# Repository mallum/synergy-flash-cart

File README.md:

# Synergy Flash Cart

A 'Flash Cart' for your DK Synergy synth... select & load ROM cartridge .crt files from the root of an SD card.

A single button cycles between .crt files placed on root of a fat formatted sd card. Top backlit character display shows currently active crt file. 

This repository contains the schematics, BOM, source code and 3D print files for a cartridge.

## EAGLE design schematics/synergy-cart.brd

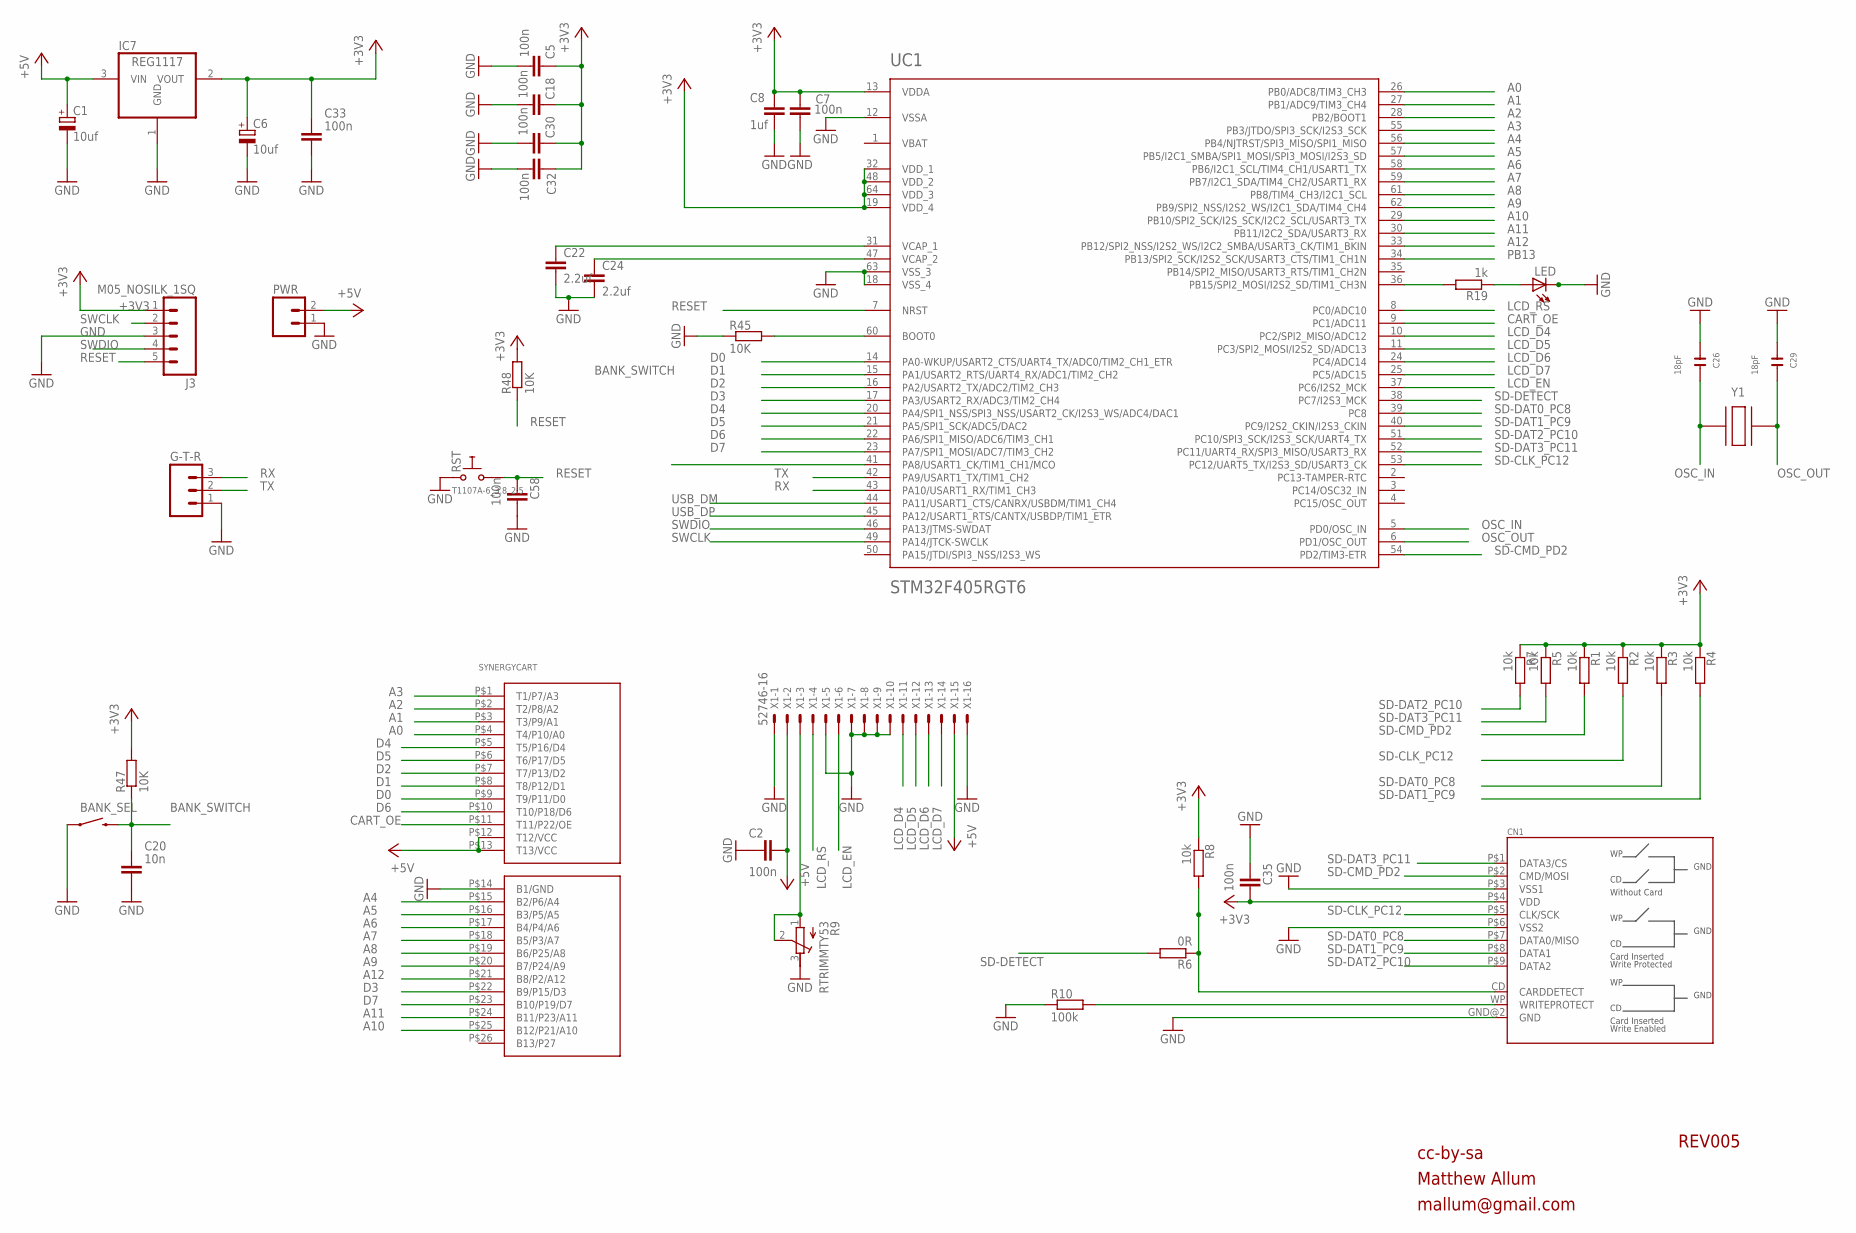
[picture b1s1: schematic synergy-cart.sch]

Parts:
BANK_SEL: SWITCH-MOMENTARY-2PTH; TACTILE-PTH
C1, C6: 10uf; CT3216
C2, C5, C7, C18, C30, C32, C33, C35, C58: 100n; C0603
C8: 1uf; C0603
C20: 10n; C0603
C22, C24: 2.2uf; C0805
C26, C29: 18pF; C0603
CN1: SDCARD160611; SDCARD_SMT_AMPH_160611
G-T-R: M03PTH; 1X03
IC7: REG1117; SOT223
J3: M05_NOSILK_1SQ
LED: LEDCHIPLED_1206; CHIPLED_1206
PWR: M02PTH; 1X02
R1, R2, R3, R4, R5, R7, R8: 10k; R0603
R6: 0R; R0603
R9: RTRIMMTY53; RTRIMTY53
R10: 100k; R0603
R19: 1k; R0603
R45, R47, R48: 10K; R0603
RST: T1107A-6_3.8_2.5; SW-TAKT_6X3.5_SMD
SYNERGYCART: SYNERGY_CARTSYNER; SYNERGY_CART
UC1: STM32F405RGT6; TQFP-10X10-64
X1: 52746-16
Y1: CRYSTAL-2; CRYSTAL-SMD-5.0MM-3.2MM-2

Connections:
+3V3: C5.1, C6.- (+), C7.1, C8.1, C18.1, C30.1, C32.1, C33.1, C35.1, CN1.P$4 (VDD), IC7.2 (VOUT), J3.1, R1.1, R2.1, R3.1, R4.1, R5.1, R7.1, R8.1, R47.2, R48.2, UC1.13 (VDDA), UC1.19 (VDD_4), UC1.32 (VDD_1), UC1.48 (VDD_2), UC1.64 (VDD_3)
+5V: C1.- (+), C2.1, IC7.3 (VIN), PWR.2, SYNERGYCART.P$12 (T12/VCC), SYNERGYCART.P$13 (T13/VCC), X1.2, X1.15
A0: SYNERGYCART.P$4 (T4/P10/A0), UC1.26 (PB0/ADC8/TIM3_CH3)
A1: SYNERGYCART.P$3 (T3/P9/A1), UC1.27 (PB1/ADC9/TIM3_CH4)
A2: SYNERGYCART.P$2 (T2/P8/A2), UC1.28 (PB2/BOOT1)
A3: SYNERGYCART.P$1 (T1/P7/A3), UC1.55 (PB3/JTDO/SPI3_SCK/I2S3_SCK)
A4: SYNERGYCART.P$15 (B2/P6/A4), UC1.56 (PB4/NJTRST/SPI3_MISO/SPI1_MISO)
A5: SYNERGYCART.P$16 (B3/P5/A5), UC1.57 (PB5/I2C1_SMBA/SPI1_MOSI/SPI3_MOSI/I2S3_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)
A6: SYNERGYCART.P$17 (B4/P4/A6), UC1.58 (PB6/I2C1_SCL/TIM4_CH1/USART1_TX)
A7: SYNERGYCART.P$18 (B5/P3/A7), UC1.59 (PB7/I2C1_SDA/TIM4_CH2/USART1_RX)
A8: SYNERGYCART.P$19 (B6/P25/A8), UC1.61 (PB8/TIM4_CH3/I2C1_SCL)
A9: SYNERGYCART.P$20 (B7/P24/A9), UC1.62 (PB9/SPI2_NSS/I2S2_WS/I2C1_SDA/TIM4_CH4)
A10: SYNERGYCART.P$25 (B12/P21/A10), UC1.29 (PB10/SPI2_SCK/I2S_SCK/I2C2_SCL/USART3_TX)
A11: SYNERGYCART.P$24 (B11/P23/A11), UC1.30 (PB11/I2C2_SDA/USART3_RX)
A12: SYNERGYCART.P$21 (B8/P2/A12), UC1.33 (PB12/SPI2_NSS/I2S2_WS/I2C2_SMBA/USART3_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)
BANK_SWITCH: BANK_SEL.3 (2), C20.1, R47.1, UC1.41 (PA8/USART1_CK/TIM1_CH1/MCO)
CART_OE: SYNERGYCART.P$11 (T11/P22/OE), UC1.9 (PC1/ADC11)
D0: SYNERGYCART.P$9 (T9/P11/D0), UC1.14 (PA0-WKUP/USART2_CTS/UART4_TX/ADC0/TIM2_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)
D1: SYNERGYCART.P$8 (T8/P12/D1), UC1.15 (PA1/USART2_RTS/UART4_RX/ADC1/TIM2_CH2)
D2: SYNERGYCART.P$7 (T7/P13/D2), UC1.16 (PA2/USART2_TX/ADC2/TIM2_CH3)
D3: SYNERGYCART.P$22 (B9/P15/D3), UC1.17 (PA3/USART2_RX/ADC3/TIM2_CH4)
D4: SYNERGYCART.P$5 (T5/P16/D4), UC1.20 (PA4/SPI1_NSS/SPI3_NSS/USART2_CK/I2S3_WS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)
D5: SYNERGYCART.P$6 (T6/P17/D5), UC1.21 (PA5/SPI1_SCK/ADC5/DAC2)
D6: SYNERGYCART.P$10 (T10/P18/D6), UC1.22 (PA6/SPI1_MISO/ADC6/TIM3_CH1)
D7: SYNERGYCART.P$23 (B10/P19/D7), UC1.23 (PA7/SPI1_MOSI/ADC7/TIM3_CH2)
GND: BANK_SEL.1, C1.+ (-), C2.2, C5.2, C6.+ (-), C7.2, C8.2, C18.2, C20.2, C22.2, C24.2, C26.2, C29.2, C30.2, C32.2, C33.2, C35.2, C58.1, CN1.GND@2 (GND), CN1.P$3 (VSS1), CN1.P$6 (VSS2), G-T-R.1, IC7.1 (GND), J3.3, LED.C, PWR.1, R9.3 (E), R10.1, R45.1, RST.P$1 (0), SYNERGYCART.P$14 (B1/GND), UC1.12 (VSSA), UC1.18 (VSS_4), UC1.63 (VSS_3), X1.1, X1.5, X1.7, X1.8, X1.9, X1.10, X1.16
LCD_D4: UC1.10 (PC2/SPI2_MISO/ADC12), X1.11
LCD_D5: UC1.11 (PC3/SPI2_MOSI/I2S2_SD/ADC13), X1.12
LCD_D6: UC1.24 (PC4/ADC14), X1.13
LCD_D7: UC1.25 (PC5/ADC15), X1.14
LCD_EN: UC1.37 (PC6/I2S2_MCK), X1.6
LCD_RS: UC1.8 (PC0/ADC10), X1.4
unnamed: R19.2, UC1.36 (PB15/SPI2_MOSI/I2S2_SD/TIM1_CH3N)
unnamed: R45.2, UC1.60 (BOOT0)
unnamed: CN1.CD (CARDDETECT), R6.1, R8.2
unnamed: CN1.WP (WRITEPROTECT), R10.2
unnamed: R9.1 (A), R9.2 (S), X1.3
unnamed: LED.A, R19.1
unnamed: C22.1, UC1.31 (VCAP_1)
unnamed: C24.1, UC1.47 (VCAP_2)
OSC_IN: C26.1, UC1.5 (PD0/OSC_IN), Y1.2
OSC_OUT: C29.1, UC1.6 (PD1/OSC_OUT), Y1.1
PB13: UC1.34 (PB13/SPI2_SCK/I2S2_SCK/USART3_CTS/TIM1_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)
RESET: C58.2, J3.5, R48.1, RST.P$2 (1), UC1.7 (NRST)
RX: G-T-R.3, UC1.43 (PA10/USART1_RX/TIM1_CH3)
SD-CLK_PC12: CN1.P$5 (CLK/SCK), R2.2, UC1.53 (PC12/UART5_TX/I2S3_SD/USART3_CK)
SD-CMD_PD2: CN1.P$2 (CMD/MOSI), R1.2, UC1.54 (PD2/TIM3-ETR)
SD-DAT0_PC8: CN1.P$7 (DATA0/MISO), R3.2, UC1.39 (PC8)
SD-DAT1_PC9: CN1.P$8 (DATA1), R4.2, UC1.40 (PC9/I2S2_CKIN/I2S3_CKIN)
SD-DAT2_PC10: CN1.P$9 (DATA2), R7.2, UC1.51 (PC10/SPI3_SCK/I2S3_SCK/UART4_TX)
SD-DAT3_PC11: CN1.P$1 (DATA3/CS), R5.2, UC1.52 (PC11/UART4_RX/SPI3_MISO/USART3_RX)
SD-DETECT: R6.2, UC1.38 (PC7/I2S3_MCK)
SWCLK: J3.2, UC1.49 (PA14/JTCK-SWCLK)
SWDIO: J3.4, UC1.46 (PA13/JTMS-SWDAT)
TX: G-T-R.2, UC1.42 (PA9/USART1_TX/TIM1_CH2)
USB_DM: UC1.44 (PA11/USART1_CTS/CANRX/USBDM/TIM1_CH4)
USB_DP: UC1.45 (PA12/USART1_RTS/CANTX/USBDP/TIM1_ETR)
VBAT: UC1.1 (VBAT)

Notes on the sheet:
REV005
cc-by-sa
Matthew Allum
mallum@gmail.com

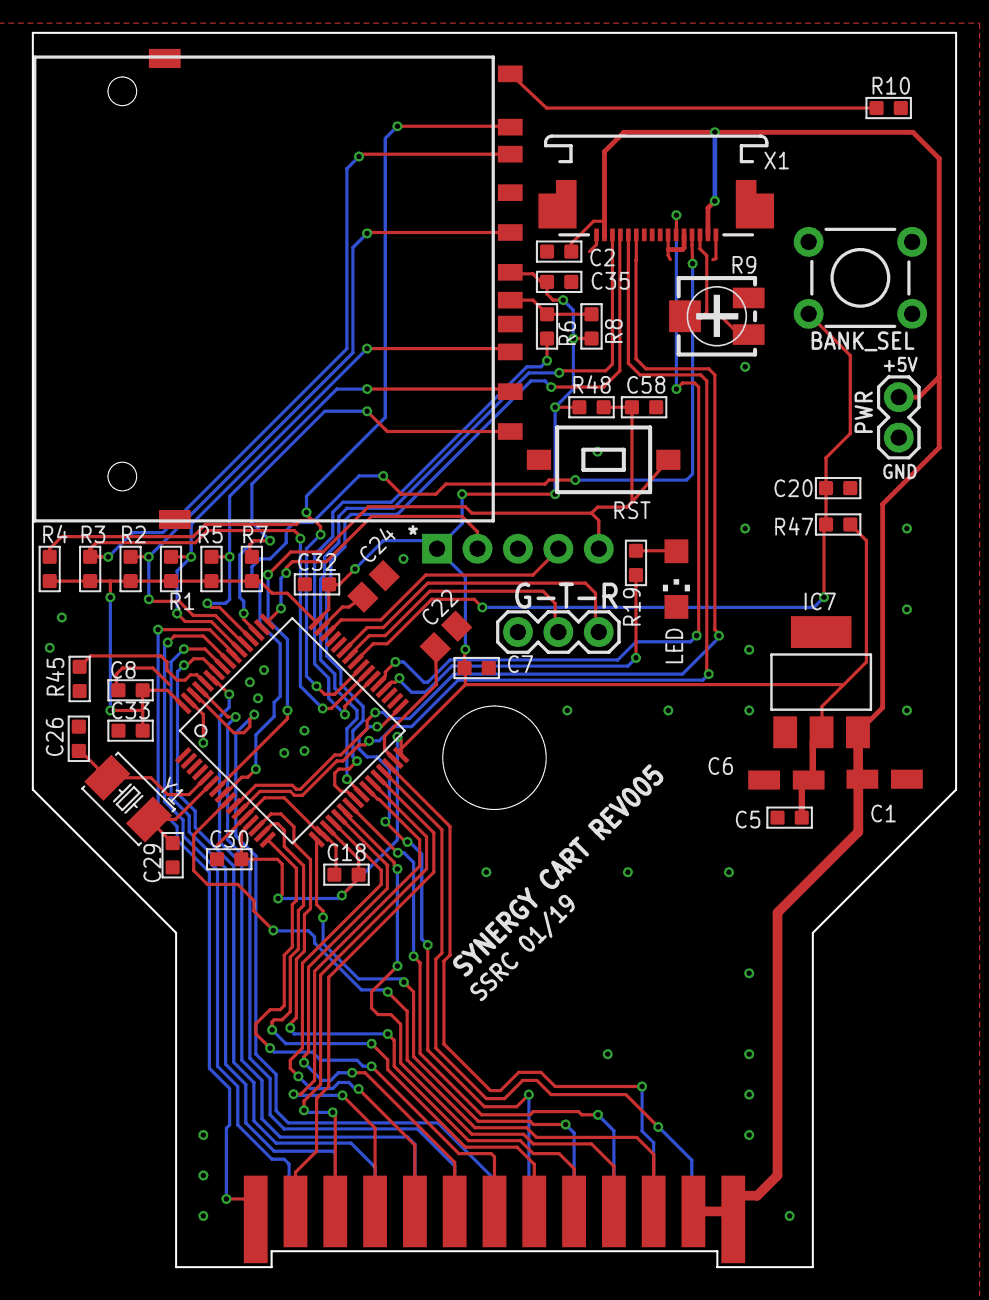
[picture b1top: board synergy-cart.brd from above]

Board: 2 copper layers, 58.0 x 77.5 mm, 43 parts (0 on the bottom side), 54 nets.

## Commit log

2019-12-30 added files
2019-12-30 fix image link
2019-12-30 more README updates

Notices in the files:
parts and their libraries:
SparkFun-Connectors: Licensing: Creative Commons ShareAlike 4.0 International - https://creativecommons.org/licenses/by-sa/4.0
